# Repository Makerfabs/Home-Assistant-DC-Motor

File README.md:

# Makerfabs Home Assistant DC Motor

## Intruduce

[Product Link](https://www.makerfabs.com/dc-motor-for-home-assistant-ga36y-555-html.html)

[Wiki Link](https://wiki.makerfabs.com/How_to_use_DC_Motor_for_Home_Assistant_GA36Y555.html)

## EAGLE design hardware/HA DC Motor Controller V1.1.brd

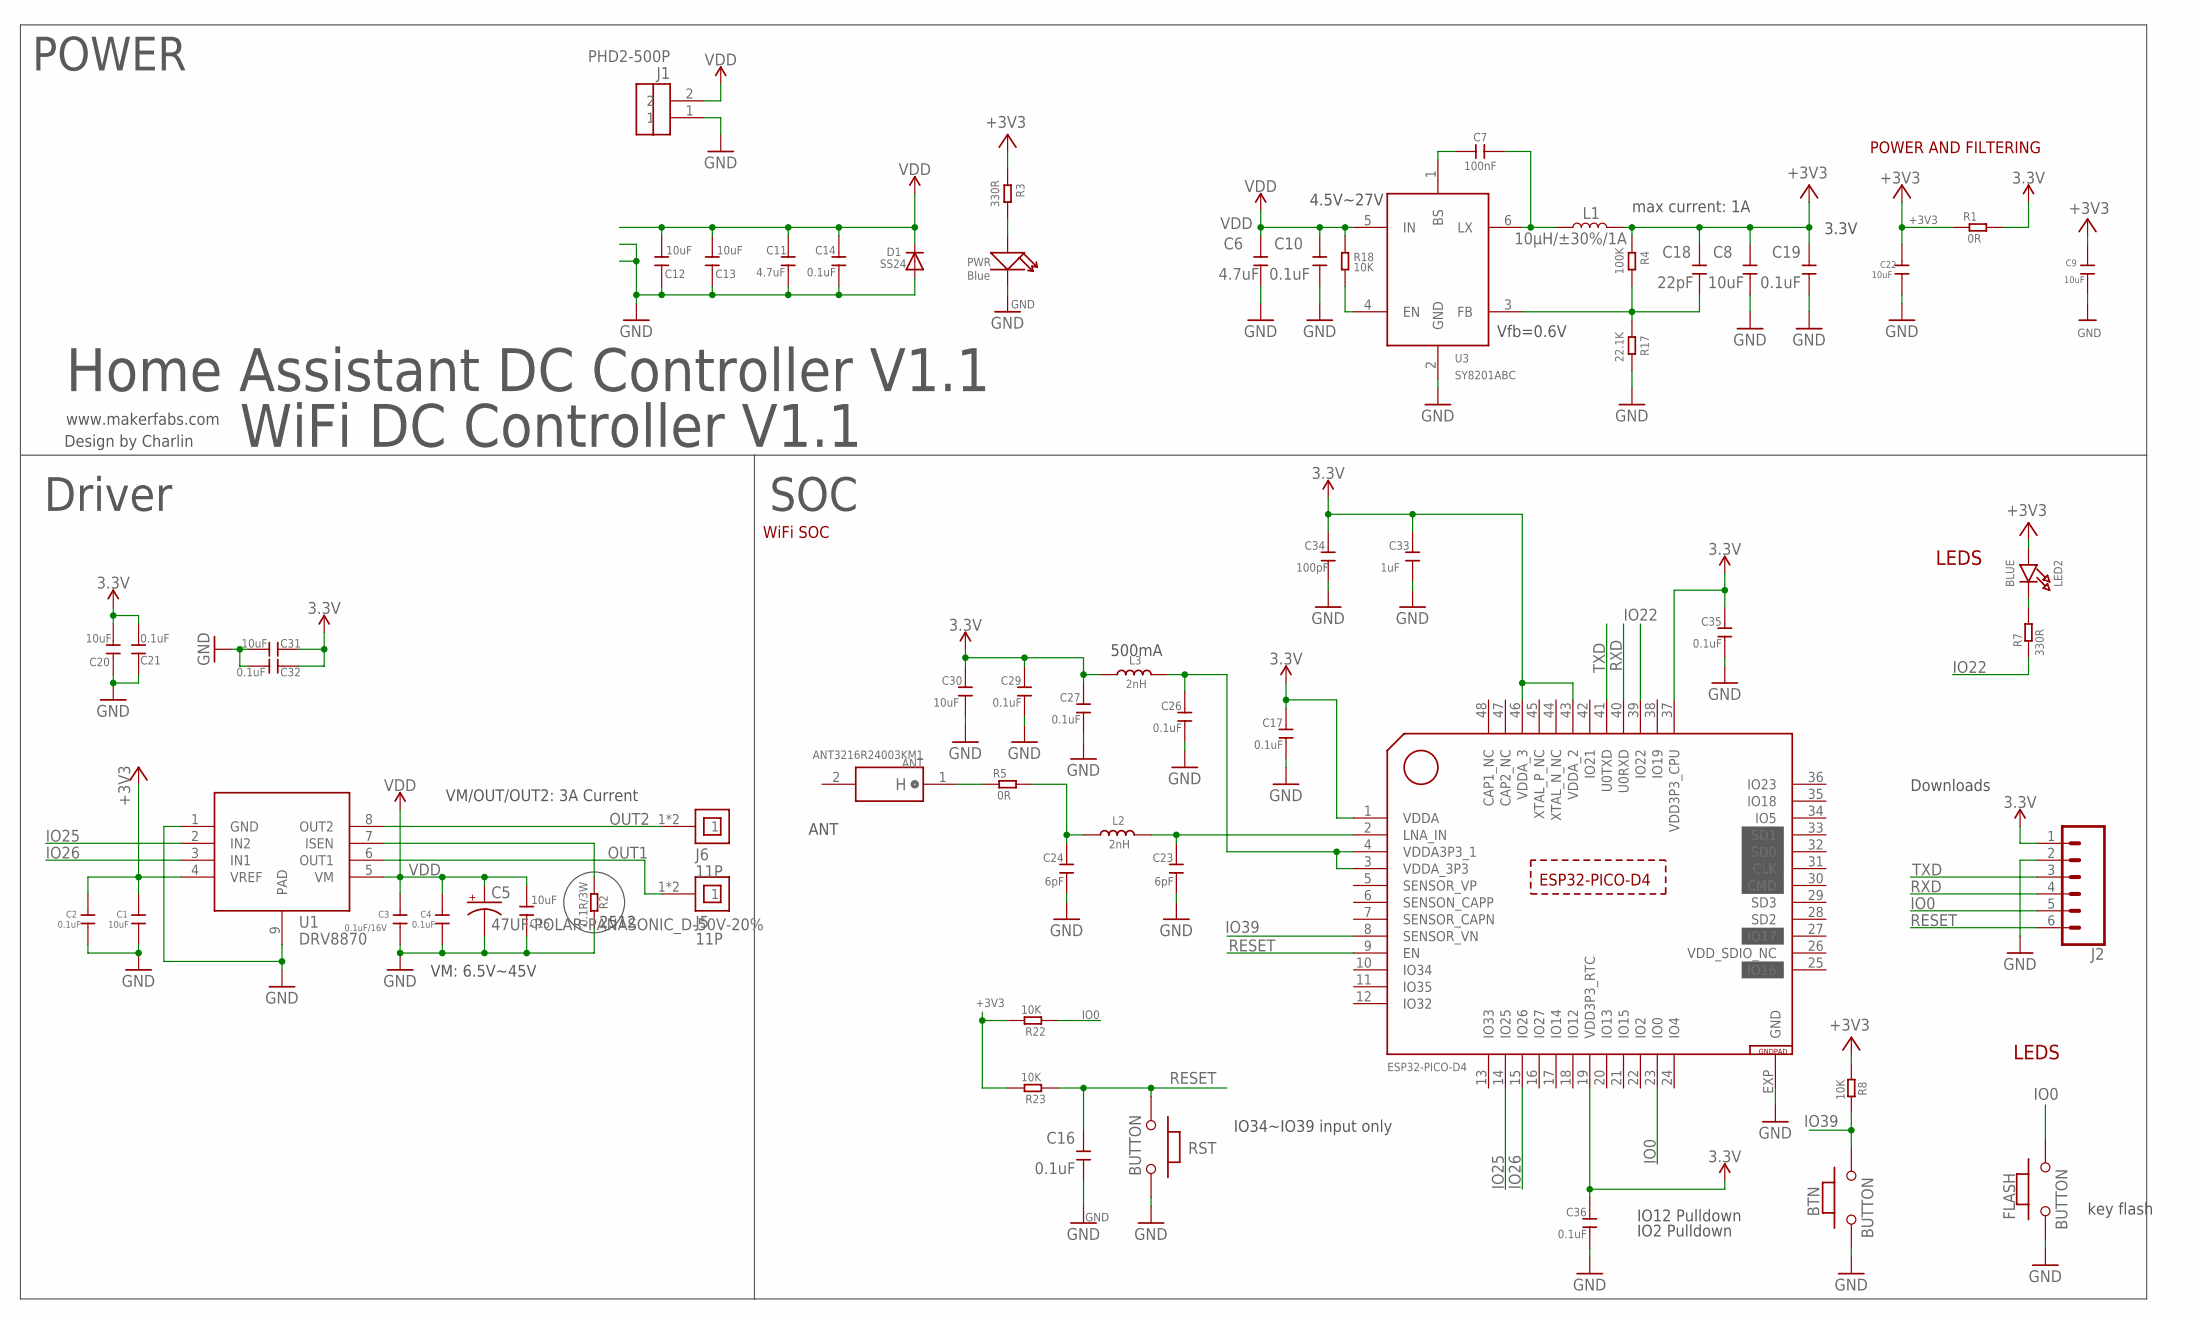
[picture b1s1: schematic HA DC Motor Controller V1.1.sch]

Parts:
ANT: ANT3216R24003KM1; ANT-1206
BTN: BUTTON; 157SW
C1, C8, C9, C22, C30: 10uF; 0603
C2, C4, C10, C14, C16, C17, C19, C26, C27, C29, C35, C36: 0.1uF; 0603
C3: 0.1uF/16V; 0603
C5: 47UF-POLAR-PANASONIC_D-50V-20%; PANASONIC_D
C6, C11: 4.7uF; 0603
C7: 100nF; 0603
C12, C13, C15: 10uF; DISCRETE_C1206
C18: 22pF; 0603
C20, C31: 10uF; DISCRETE_C0603
C21, C32: 0.1uF; DISCRETE_C0603
C23, C24: 6pF; 0603
C33: 1uF; 0603
C34: 100pF; 0603
D1: SS24; SMADIODE
FLASH: BUTTON; 157SW
J1: PHD2-500P; OPL_EAGLE_LIBRARY_2P-5.0
J2: CONN_06SILK_FEMALE_PTH; 1X06
J5, J6: 11P; 1*1P-4*1MM
L1: 10µH/±30%/1A; CR54
L2, L3: 2nH; DISCRETE_L0603
LED2: BLUE; CHIPLED_0805_NOOUTLINE
PWR: Blue; LED-0603
R1, R5: 0R; R0603
R2: 0.1R/3W; DISCRETE_R2512
R3, R7: 330R; R0603
R4: 100K; R0603
R8, R18, R22, R23: 10K; R0603
R17: 22.1K; R0603
RST: BUTTON; 157SW
U1: DRV8870; SOP-8-EP
U3: SY8201ABC; SOT-23-6
U$2: ESP32-PICO-D4; QFN48

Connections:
3.3V: C17.2, C20.2, C21.2, C27.2, C29.2, C30.2, C31.1, C32.1, C33.2, C34.2, C35.2, C36.2, J2.1, L3.1, R1.2, U$2.1 (VDDA), U$2.19 (VDD3P3_RTC), U$2.37 (VDD3P3_CPU), U$2.43 (VDDA_2), U$2.46 (VDDA_3)
+3V3: C1.1, C2.1, C8.2, C9.1, C18.2, C19.2, C22.1, L1.P$2 (2), LED2.A, R1.1, R3.1, R4.1, R8.1, R22.2, R23.2, U1.4 (VREF)
GND: BTN.1, C1.2, C2.2, C3.2, C4.2, C5.-, C6.1, C8.1, C9.2, C10.1, C11.1, C12.1, C13.1, C14.1, C15.1, C16.1, C17.1, C19.1, C20.1, C21.1, C22.2, C23.1, C24.1, C26.1, C27.1, C29.1, C30.1, C31.2, C32.2, C33.1, C34.1, C35.1, C36.1, D1.A, FLASH.1, J1.1, J2.2, PWR.-, R2.1, R17.2, RST.1, U1.1 (GND), U1.9 (PAD), U3.2 (GND), U$2.EXP (GND)
IO0: FLASH.2, J2.5, R22.1, U$2.23 (IO0)
IO22: R7.1, U$2.39 (IO22)
IO25: U1.2 (IN2), U$2.14 (IO25)
IO26: U1.3 (IN1), U$2.15 (IO26)
IO39: BTN.2, R8.2, U$2.8 (SENSOR_VN)
unnamed: PWR.+, R3.2
unnamed: C7.2, L1.P$1 (1), U3.6 (LX)
unnamed: C7.1, U3.1 (BS)
unnamed: R2.2, U1.7 (ISEN)
unnamed: C18.1, R4.2, R17.1, U3.3 (FB)
unnamed: R18.2, U3.4 (EN)
unnamed: C26.2, L3.2, U$2.3 (VDDA_3P3), U$2.4 (VDDA3P3_1)
unnamed: C23.2, L2.2, U$2.2 (LNA_IN)
unnamed: C24.2, L2.1, R5.2
unnamed: ANT.1, R5.1
unnamed: LED2.C, R7.2
OUT1: J5.1, J5.1@1, U1.6 (OUT1)
OUT2: J6.1, J6.1@1, U1.8 (OUT2)
RESET: C16.2, J2.6, R23.1, RST.2, U$2.9 (EN)
RXD: J2.4, U$2.40 (U0RXD)
TXD: J2.3, U$2.41 (U0TXD)
VDD: C3.1, C4.1, C5.+, C6.2, C10.2, C11.2, C12.2, C13.2, C14.2, C15.2, D1.C, J1.2, R18.1, U1.5 (VM), U3.5 (IN)
VDD_SDIO_NC: U$2.26 (VDD_SDIO_NC)

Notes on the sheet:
www.makerfabs.com
Design by Charlin
LEDS
POWER AND FILTERING
WiFi SOC
key flash
Home Assistant DC Controller V1.1
IO34~IO39 input only
POWER
SOC
VM/OUT/OUT2: 3A Current
VM: 6.5V~45V
2512
Vfb=0.6V
3.3V
4.5V~27V
max current: 1A
IO12 Pulldown
IO2 Pulldown
500mA
ANT
Downloads
WiFi DC Controller V1.1
Driver

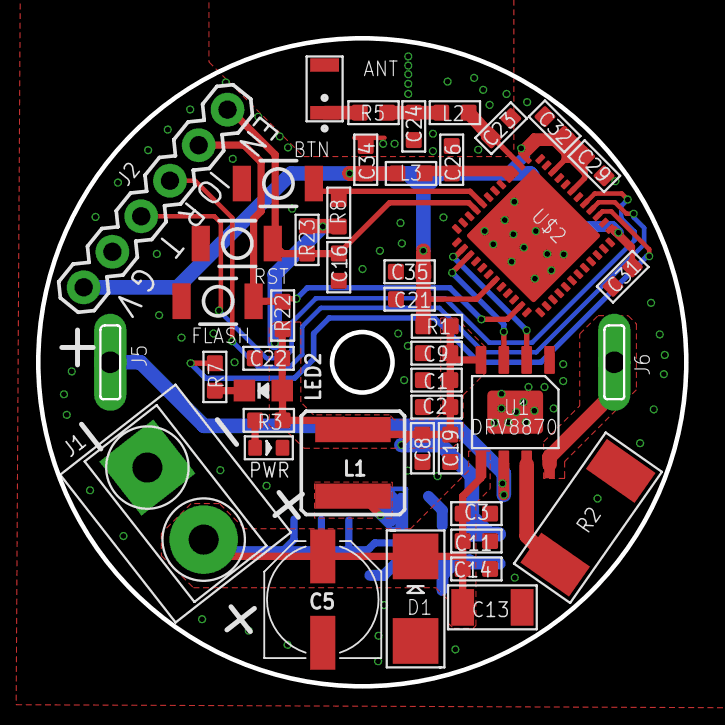
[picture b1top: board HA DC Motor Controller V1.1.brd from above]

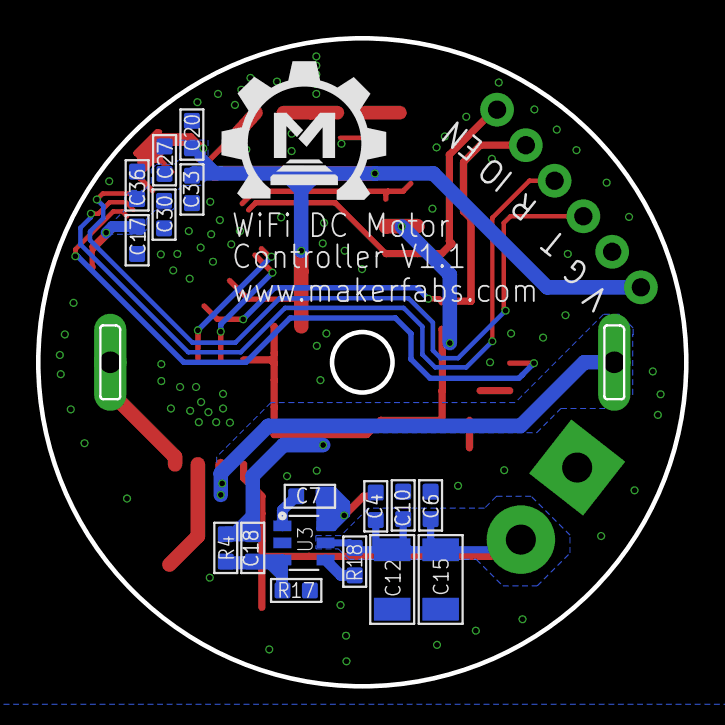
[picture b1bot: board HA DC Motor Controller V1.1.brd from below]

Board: 2 copper layers, 36.0 x 36.0 mm, 63 parts (18 on the bottom side), 25 nets.

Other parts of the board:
U$1: MAKERFABS_0.3

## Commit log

2023-09-13 Create
2023-09-15 Add hardware
2023-10-23 V1.1 Add endstop
2025-09-27 update README.md&yaml

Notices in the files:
parts and their libraries:
microbuilder: This work is placed in the public domain, and may be freely used for commercial and non-commercial work with the following conditions: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
SparkFun-Capacitors: Licensing: Creative Commons ShareAlike 4.0 International - https://creativecommons.org/licenses/by-sa/4.0
